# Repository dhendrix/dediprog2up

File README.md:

# dediprog2up

This is an adapter intended to make firmware development easier on UP Xtreme
and UP Squared motherboards using Dediprog SF600 and EM100.

This project started as I was thinking about playing with the system firmware
(BIOS) on the UP Xtreme and trying to do a coreboot port. I had limited success
at creating a custom cable with a 12-pin header on one side and a 20-pin header
on the other to fit on a [Dediprog
ADP-SF600-254-TO-127-CB](https://www.dediprog.com/product/ADP-SF600-254-TO-127-CB).
It was difficult to split a fine-pitch ribbon cable and when I finally got one
working it could only operate at 1.5MHz.

Using this adapter board I was able to read and write the ROM using an SF600 at
24MHz, which is also fast enough to use an EM100 for SPI flash emulation.

## Pinout
### UP

The UP wiki has a good diagram of the header:
https://wiki.up-community.org/BIOS_chip_flashing_on_UP_Squared

I probed all the pins to verify the UP wiki's pinout. I'm still not sure which
pin is write-protect or if the extra 4 pins are used for anything (the flash
chip only has 8 pins), so if you happen to know feel free to send a PR to
update this README or file an issue to let me know!

The header is 2x6, pitch is 1.27mm.

Pin | Signal | Signal | Pin
:-: | :----: | :----: | :--:
1   |  GND   |  GND   |  2
3   |  GND   |  VCC   |  4
5   |  VCC   |  /CS   |  6
7   |  CLK   |  MISO  |  8
9   |  VCC   |  GND   | 10
11  | MOSI   |  /HOLD | 12

### Dediprog SF600/EM100

The header is 2x10, pitch is 2.54mm

The pinout is printed on the device, but here is a simplified version for our
purposes:

Pin | Signal | Signal | Pin
:-: | :----: | :----: | :--:
1   |  NC    |    NC  |  2
3   |  /CS   |   VCC  |  4
5   |  MISO  | /HOLD  |  6
7   |  NC    |   CLK  |  8
9   |  GND   |  MOSI  | 10
11  |  NC    |    NC  | 12
13  |  NC    |    NC  | 14
15  |  NC    |    NC  | 16
17  |  NC    |    NC  | 18
19  |  NC    |    NC  | 20

## Fabricating the adapter

There are a few online PCB fabrication companies. For this project I used
Oshpark since they make it super-easy to order boards that were made with
KiCad. Just upload the .kicad_pcb file to their website and they'll do the
rest.

Here is a project page at Oshpark where you can order directly:
https://oshpark.com/shared_projects/HCAx2AVW

## Additional Parts
### Headers

12-pin header to plug cable into:
https://www.chipquik.com/store/product_info.php?products_id=1900044

20-pin connector to plug into SF600/EM100:
https://www.digikey.com/en/products/detail/sullins-connector-solutions/SFH11-PBPC-D10-ST-BK/1990090

Top view with headers soldered on

Bottom view with headers soldered on

### Cable

One thing to keep in mind when working with SPI flash is that shorter cables
are better. Up to 4 inches / 10 centimeters is generally OK, but above that you
may need to slow down your programmer's clock frequency. If you can use a
shorter cable then it's recommended that you do so.

The UP Xtreme's pin header is squeezed in between the HDMI/DP connector and the
RTC battery header. You'll likely need to cut (e.g. using a Dremel) the sides
of the receptacle on one end of the cable - be sure you do so on the side that
plug into the board. This unfortunately makes it easy for the receptacle to
fall apart, so be careful when handling the cable once it's plugged in.

#### Premade cables

12-pin 1.27mm pitch cables are somewhat rare and expensive, but come with some
assurance of quality so it's not a bad idea to have one.

Here is a pre-made cable on Mouser:
https://www.mouser.com/ProductDetail/200-FFSD06D04.0001N

#### DIY cables

It's somewhat easier to find the parts needed to make a 12-pin 1.27mm pitch
cable than finding a premade cable.

Ribbon cable:
https://www.mouser.com/ProductDetail/Wurth-Elektronik/63911215521CAB?qs=rrS6PyfT74fhArRJ3tCNFA%3D%3D

IDC header:
https://www.mouser.com/ProductDetail/Harwin/M50-3300642?qs=lPIp2VBpF5j6R5jWq4Rd4A%3D%3D

## Flash Chip

The flash chip on the UP Xtreme is a 1.8V W25Q256JWEQ. The flash chip on the UP
Squared is a 1.8V W25Q128FW (according to the UP Wiki).

I've been able to successfully read it at 24MHz which is the highest speed the
SF600 supports. It is recommended to read the chip several times and diff the
output to ensure consistent readings.  Inconsistent readings may indicate that
your cable is too long or that there is a quality issue with your cable or
soldering.

Here is how to read it using flashrom:

	flashrom -p dediprog:voltage=1.8,spispeed=24M -r foo.bin

# Related projects

* A similar adapter for UP boards intended to work with Dediprog hardware:
  https://github.com/skiselev/up-dediprog-adapter

* The qspimux project has adapters for several popular NOR flash sockets and
  adds isolatation circuitry to eliminate potential errors while also making it
  suitable for programmers that are always-on:
  https://github.com/felixheld/qspimux

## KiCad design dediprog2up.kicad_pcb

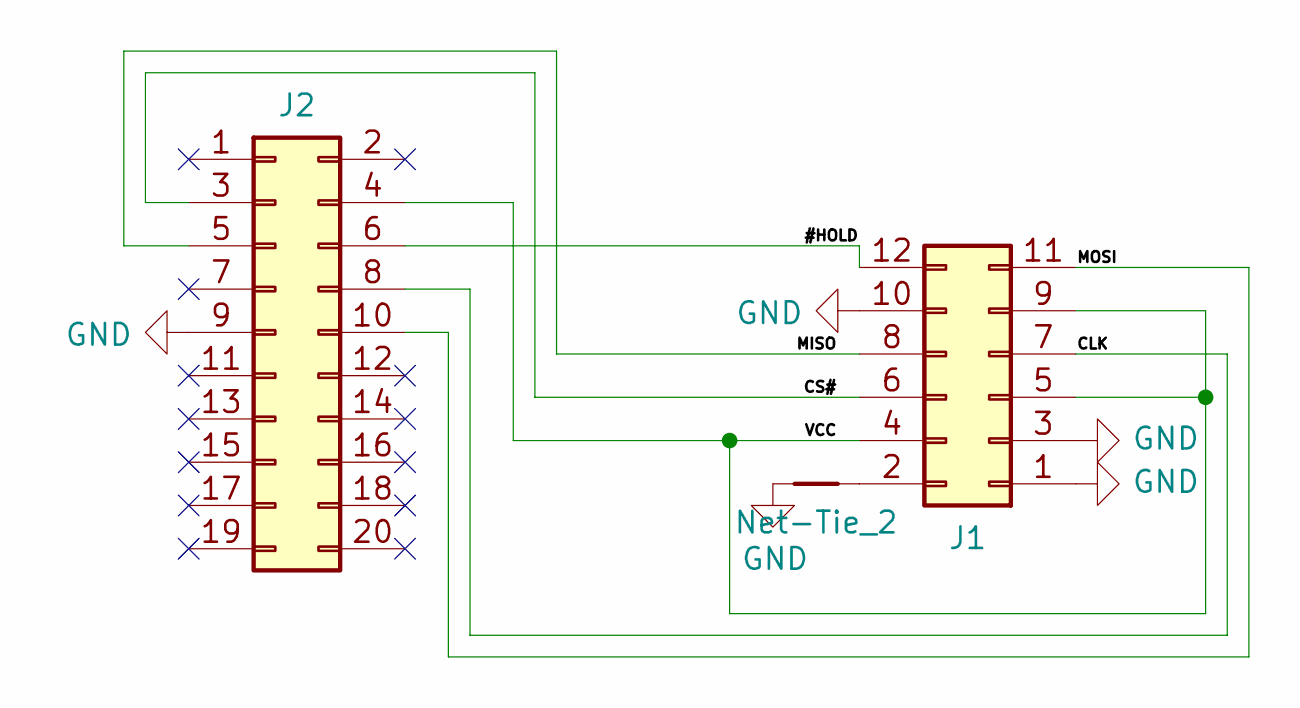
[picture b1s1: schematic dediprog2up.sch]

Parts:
GND1: Net-Tie_2; NetTie-2_SMD_Pad0.5mm
J1: Conn_02x6_Odd_Even; PinHeader_2x06_P1.27mm_Vertical
J2: Conn_02x10_Odd_Even; PinHeader_2x10_P2.54mm_Vertical

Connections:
/#HOLD: J1.12, J2.6
/CLK: J1.7, J2.8
/CS#: J1.6, J2.3
/MISO: J1.8, J2.5
/MOSI: J1.11, J2.10
/VCC: J1.4, J1.5, J1.9, J2.4
GND: GND1.2, J1.1, J1.3, J1.10, J2.9
unnamed: GND1.1, J1.2

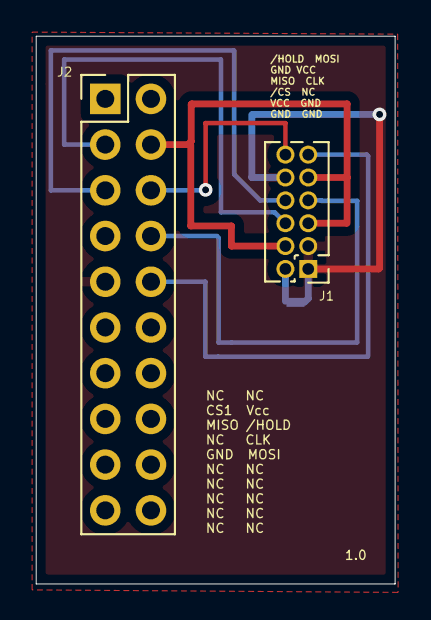
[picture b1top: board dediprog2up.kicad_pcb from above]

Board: 2 copper layers, 19.9 x 30.4 mm, 3 parts (1 on the bottom side), 8 nets.

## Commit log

2020-10-04 Add .gitignore
2020-10-04 Add repository URL in schematic
2020-10-04 Add images for README
2023-12-27 Update README.md
    - Add links to related projects.
    - Add link to Oshpark for easy ordering.
    - Reword a few sentences.
2023-12-27 Reflow text in README.md

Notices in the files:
dediprog2up.kicad_pcb:
License: CC BY 4.0
dediprog2up.sch:
creativecommons.org/licenses/by/4.0
